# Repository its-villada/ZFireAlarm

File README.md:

# ZFireAlarm
Sistema de sensores inalámbricos a ser distribuidos sobre el edificio de la institución educativa para lograr el objetivo inicial de red inalámbrica para sirenas de incendio.

## Objetivos
- Que el alumno se familiarice con las capacidades de los equipos XBee.
- Que sea capaz de diseñar una parte de un sistema real, que luego se montará en la práctica.
- Definir un presupuesto real para implementar un sistema completo y revisar posibilidades de implementación en base a disponibilidad en el mercado.
- Adquirir nociones generales sobre el hardware y software a utilizar en aplicaciones reales, a través del desarrollo de un ejercicio práctico aplicado a sensores y actuadores remotos. 

## Software y aplicaciones
- Python: https://www.python.org/
- Python-XBee: https://pypi.python.org/pypi/XBee
- XCTU: http://www.digi.com/products/xbee-rf-solutions/xctu-software/

## Arquitectura del sistema

### Gateway
El gateway debe estar montado con un Raspberry Pi (https://www.raspberrypi.org/) incluyendo un modulo XBee. En el siguiente link pueden encontrar un ejemplo de shield para XBee en la plataforma: https://www.cooking-hacks.com/ocumentation/tutorials/xbee-arduino-raspberry-pi-tutorial/

Las características son:
- El raspberry pi a utilizar es Raspberry Pi Model B+ (B PLUS) 512MB
- Conectividad ethernet (provista a través del Raspberry pi)
- Modulo XBee pro series 2: https://cdn-shop.adafruit.com/product-files/967/p967b+datasheet.pdf
- El shield de xbee provee un conector para puerto serie (idéntico al utilizado en las placas XBoard)
- Alimentado con fuente de alimentación externa
- Led indicador de alimentación.
- Entrada para pulsador externo (activación principal de la alarma de incendio).

### Nodos

Las características de los nodos son:
- Bateria 12V 7 A/H , las mismas que se utilizan en los sistemas de alarmas hogareño.
- Led indicador estado de batería
- Conector serie (idéntico al utilizado en las placas de evaluacion XBoard)
- Salida para alimentar una sirena 12V/24V 2A.
- Conectividad wireless brindada por módulo XBee pro series 2.

## Hardware
- Sirenas incendio
- Modulos XBee pro
- Modulo Raspberri pi
- Gabinete
- Bateria 12V 7AH

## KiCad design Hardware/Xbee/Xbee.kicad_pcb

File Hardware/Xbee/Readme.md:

# Diseño en KiCad

Se utiliza una única placa con ambas funciones.
Esquemático en Xbee.pdf

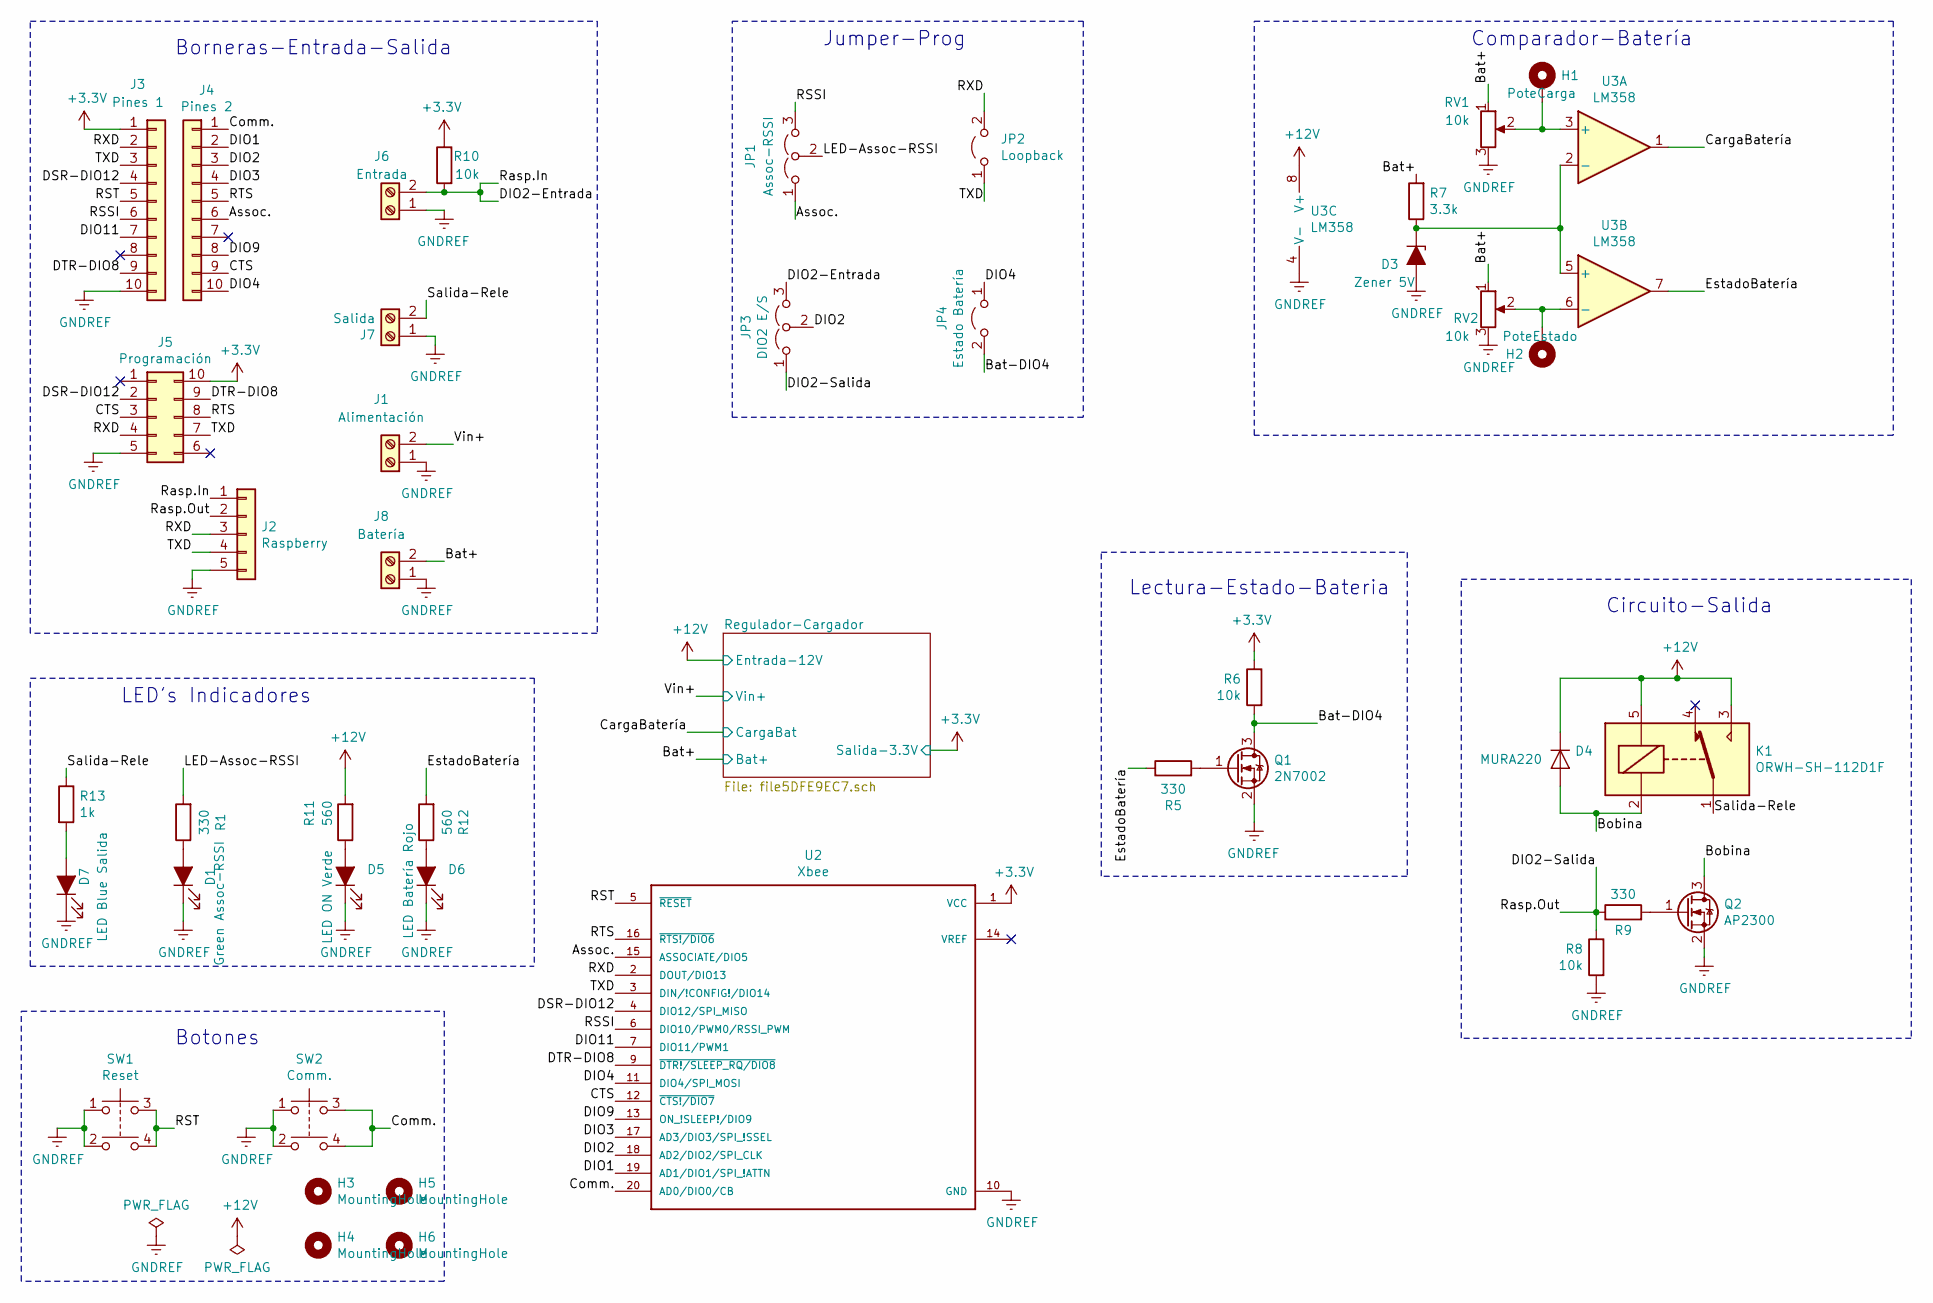
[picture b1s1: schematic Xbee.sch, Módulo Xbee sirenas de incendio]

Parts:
D1: Green Assoc-RSSI; LED_1206_3216Metric_Pad1.42x1.75mm_HandSolder
D3: Zener 5V; D_SOT-23_ANK
D4: MURA220; D_SMA_Handsoldering
D5: LED ON Verde; PinSocket_1x02_P2.54mm_Vertical
D6: LED Batería Rojo; PinSocket_1x02_P2.54mm_Vertical
D7: LED Blue Salida; LED_1206_3216Metric_Pad1.42x1.75mm_HandSolder
H1: PoteCarga; MountingHole_2.2mm_M2_DIN965_Pad
H2: PoteEstado; MountingHole_2.2mm_M2_DIN965_Pad
H3, H4, H5, H6: MountingHole; MountingHole_3.2mm_M3
J1: Alimentación; TerminalBlock_bornier-2_P5.08mm
J2: Raspberry; PinHeader_1x05_P2.54mm_Vertical
J3: Pines 1; PinSocket_1x10_P2.00mm_Vertical
J4: Pines 2; PinSocket_1x10_P2.00mm_Vertical
J5: Programación; PinSocket_2x05_P2.54mm_Horizontal
J6: Entrada; TerminalBlock_bornier-2_P5.08mm
J7: Salida; TerminalBlock_bornier-2_P5.08mm
J8: Batería; TerminalBlock_bornier-2_P5.08mm
JP1: Assoc-RSSI; PinHeader_1x03_P2.54mm_Vertical
JP2: Loopback; PinHeader_1x02_P2.54mm_Vertical
JP3: DIO2 E/S; PinHeader_1x03_P2.54mm_Vertical
JP4: Estado Batería; PinHeader_1x02_P2.54mm_Vertical
K1: ORWH-SH-112D1F; Relay_SPDT_SANYOU_SRD_Series_Form_C
Q1: 2N7002; SOT-23
Q2: AP2300; SOT-23
R1, R5, R9: 330; R_1206_3216Metric_Pad1.42x1.75mm_HandSolder
R6, R8, R10: 10k; R_1206_3216Metric_Pad1.42x1.75mm_HandSolder
R7: 3.3k; R_1206_3216Metric_Pad1.42x1.75mm_HandSolder
R11, R12: 560; R_1206_3216Metric_Pad1.42x1.75mm_HandSolder
R13: 1k; R_1206_3216Metric_Pad1.42x1.75mm_HandSolder
RV1, RV2: 10k; Potentiometer_Vishay_T73YP_Vertical
SW1: Reset; SW_TH_Tactile_Omron_B3F-10xx
SW2: Comm.; SW_TH_Tactile_Omron_B3F-10xx
U2: Xbee; DIP2200W51P200L3294H279Q20P
U3: LM358; SO-8_3.9x4.9mm_P1.27mm

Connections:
+3V3: J3.1, J5.10, R6.1, R10.1, U2.1 (VCC); also elsewhere on the board
+12V: D4.1 (K), K1.3, K1.5, R11.2, U3.8 (V+); also elsewhere on the board
/Assoc.: J4.6, JP1.1 (A), U2.15 (ASSOCIATE/DIO5)
/Bat+: J8.2, R7.2, RV1.1, RV2.1; also elsewhere on the board
/Bat-DIO4: JP4.2 (B), Q1.3 (D), R6.2
/Bobina: D4.2 (A), K1.2, Q2.3 (D)
/CTS: J4.9, J5.3, U2.12 (~CTS!/DIO7~)
/CargaBatería: U3.1; also elsewhere on the board
/Comm.: J4.1, SW2.3, SW2.4, U2.20 (AD0/DIO0/CB)
/DIO1: J4.2, U2.19 (AD1/DIO1/SPI_!ATTN)
/DIO2: J4.3, JP3.2 (C), U2.18 (AD2/DIO2/SPI_CLK)
/DIO2-Entrada: J2.1, J6.2, JP3.3 (B), R10.2
/DIO2-Salida: J2.2, JP3.1 (A), R8.1, R9.1
/DIO3: J4.4, U2.17 (AD3/DIO3/SPI_!SSEL)
/DIO4: J4.10, JP4.1 (A), U2.11 (DIO4/SPI_MOSI)
/DIO9: J4.8, U2.13 (ON_!SLEEP!/DIO9)
/DIO11: J3.7, U2.7 (DIO11/PWM1)
/DSR-DIO12: J3.4, J5.2, U2.4 (DIO12/SPI_MISO)
/DTR-DIO8: J3.9, J5.9, U2.9 (~DTR!/SLEEP_RQ/DIO8~)
/EstadoBatería: R5.1, R12.2, U3.7
/LED-Assoc-RSSI: JP1.2 (C), R1.2
/RSSI: J3.6, JP1.3 (B), U2.6 (DIO10/PWM0/RSSI_PWM)
/RST: J3.5, SW1.3, SW1.4, U2.5 (~RESET~)
/RTS: J4.5, J5.8, U2.16 (~RTS!/DIO6~)
/RXD: J2.3, J3.2, J5.4, JP2.2 (B), U2.2 (DOUT/DIO13)
/Salida-Rele: J7.2, K1.1, R13.1
/TXD: J2.4, J3.3, J5.7, JP2.1 (A), U2.3 (DIN/!CONFIG!/DIO14)
/Vin+: J1.2; also elsewhere on the board
GNDREF: D1.1 (K), D3.2 (A), D5.1 (K), D6.1 (K), D7.1 (K), J1.1, J2.5, J3.10, J5.5, J6.1, J7.1, J8.1, Q1.2 (S), Q2.2 (S), R8.2, RV1.3, RV2.3, SW1.1, SW1.2, SW2.1, SW2.2, U2.10 (GND), U3.4 (V-); also elsewhere on the board
unnamed: D1.2 (A), R1.1
unnamed: D3.1 (K), R7.1, U3.2 (-), U3.5 (+)
unnamed: D5.2 (A), R11.1
unnamed: D6.2 (A), R12.1
unnamed: D7.2 (A), R13.2
unnamed: H1.1, RV1.2, U3.3 (+)
unnamed: H2.1, RV2.2, U3.6 (-)
unnamed: Q1.1 (G), R5.2
unnamed: Q2.1 (G), R9.2

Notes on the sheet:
Borneras-Entrada-Salida
LED's Indicadores
Jumper-Prog
Circuito-Salida
Comparador-Batería
Botones
Lectura-Estado-Bateria

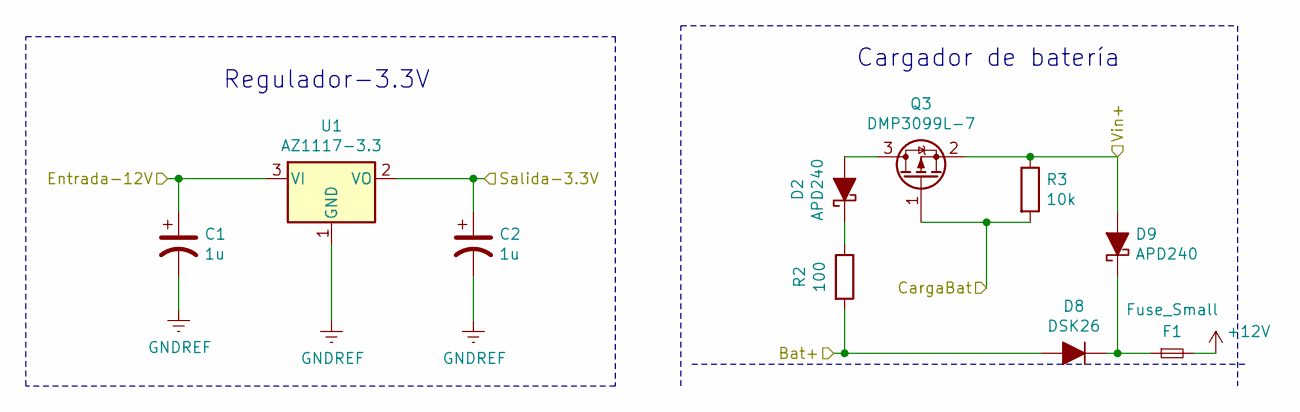
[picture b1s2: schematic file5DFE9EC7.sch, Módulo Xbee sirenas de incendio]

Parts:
C1, C2: 1u; C_0805_2012Metric_Pad1.15x1.40mm_HandSolder
D2, D9: APD240; D_SOD-123
D8: DSK26; D_SOD-123F
F1: Fuse_Small; Fuse_1206_3216Metric_Pad1.42x1.75mm_HandSolder
Q3: DMP3099L-7; SOT-23
R2: 100; R_1218_3246Metric_Pad1.22x4.75mm_HandSolder
R3: 10k; R_1206_3216Metric_Pad1.42x1.75mm_HandSolder
U1: AZ1117-3.3; SOT-223-3_TabPin2

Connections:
+3V3: C2.1, U1.2 (VO); also elsewhere on the board
+12V: C1.1, F1.2, U1.3 (VI); also elsewhere on the board
/Bat+: D8.2 (A), R2.2; also elsewhere on the board
/CargaBatería: Q3.1 (G), R3.2; also elsewhere on the board
/Vin+: D9.2 (A), Q3.2 (S), R3.1; also elsewhere on the board
GNDREF: C1.2, C2.2, U1.1 (GND); also elsewhere on the board
unnamed: D2.1 (K), R2.1
unnamed: D2.2 (A), Q3.3 (D)
unnamed: D8.1 (K), D9.1 (K), F1.1

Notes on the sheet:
Regulador-3.3V
Cargador de batería

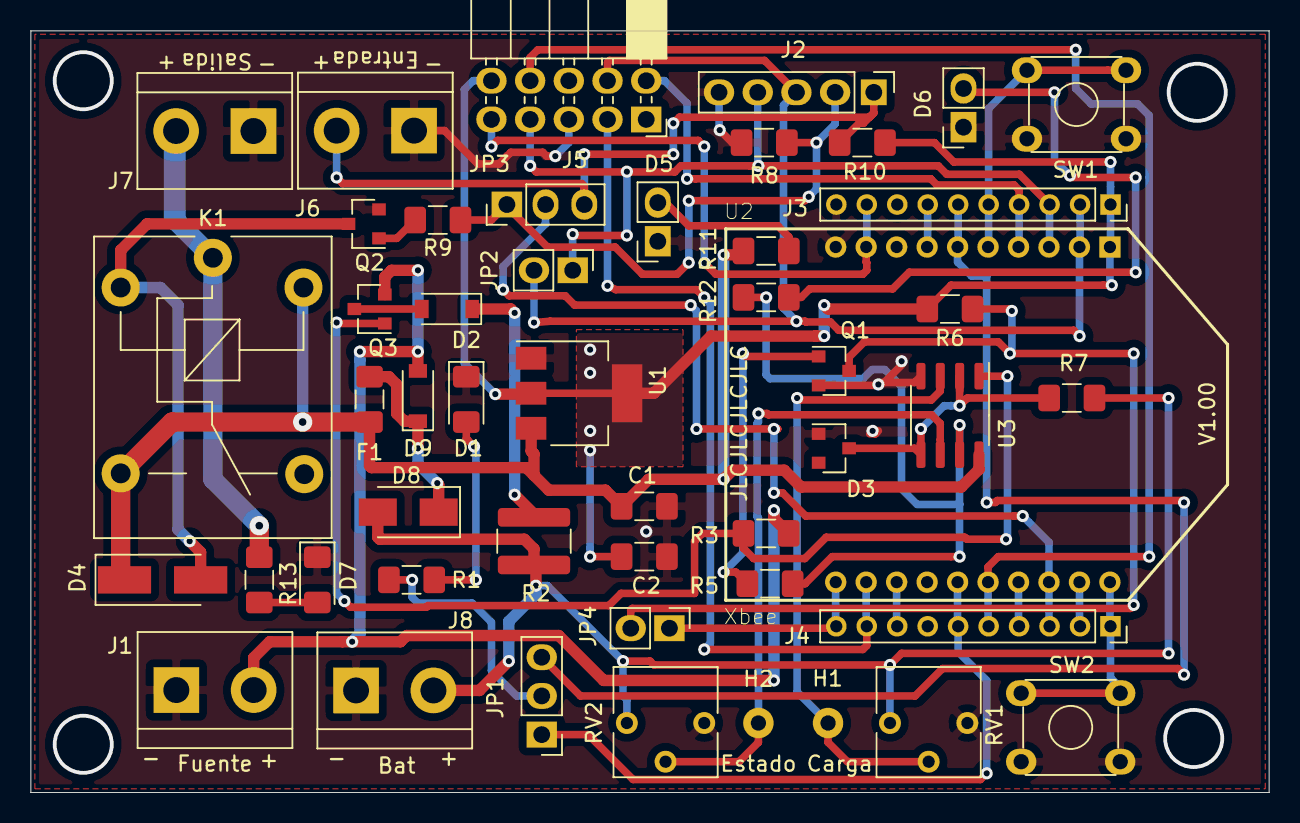
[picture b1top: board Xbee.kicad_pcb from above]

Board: 2 copper layers, 81.3 x 50.0 mm, 49 parts (0 on the bottom side), 41 nets.

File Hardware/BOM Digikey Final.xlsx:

Qty | Value | Código Proveedor 1 | Código Proveedor 2 | Package | Costo Unit. [u$] | Total [u$] | Total [$] | Dolar: | 62
2 | 1u | 399-8150-1-ND |  | 1206 | 0.19 | 0.38 | 23.56 |  |  |  | Costo Tot [u$] | 19.03
1 | Green Assoc-RSSI | 160-1169-1-ND |  | 1206 | 0.33 | 0.33 | 20.46
2 | MBR230LSTR | 1655-2311-1-ND |  | SOD-123 | 0.36 | 0.72 | 44.64 |  |  |  | Costo Tot [$] | 1179.8600000000001
1 | Zener 5V | BZX84C5V1LT3GOSCT-ND |  | SOT-23 | 0.13 | 0.13 | 8.06
1 | MURA260T3G | MURA260T3GOSCT-ND |  | SMA | 0.35 | 0.35 | 21.7 |  |  |  | Costo Tot [$] (x15) | 17697.900000000001
1 | LED ON Verde | 160-1131-ND |  | 5mm T/H | 0.27 | 0.27 | 16.740000000000002
1 | LED Rojo | 365-1189-ND |  | 5mm T/H | 0.21 | 0.21 | 13.02
1 | LED Blue Salida | 732-4989-1-ND |  | 1206 | 0.21 | 0.21 | 13.02
1 | MURA260T3G | MURA260T3GOSCT-ND |  | SMA | 0.35 | 0.35 | 21.7
1 | Fuse_Small | 507-1881-1-ND |  | 1206 | 0.28999999999999998 | 0.28999999999999998 | 17.98
1 | Alimentación | 102-6422-ND |  | 5.08mm T/H | 0.46 | 0.46 | 28.52
1 | Alimentación 2 | 102-6390-ND |  | 5.08mm T/H | 0.77 | 0.77 | 47.74
1 | Raspberry | 2057-PH1-05-UA-ND |  | 2.54mm T/H | 0.1 | 0.1 | 6.2
1 | Pines 1 | 1212-1314-ND |  | 2mm T/H | 0.91 | 0.91 | 56.42
1 | Pines 2 | 1212-1314-ND |  | 2mm T/H | 0.91 | 0.91 | 56.42
1 | Programaci√≥n | S9202-ND |  | 2.54mm T/H | 0.8 | 0.8 | 49.6
1 | Entrada | 102-6422-ND |  | 5.08mm T/H | 0.46 | 0.46 | 28.52
1 | Entrada 2 | 102-6390-ND |  | 5.08mm T/H | 0.77 | 0.77 | 47.74
1 | Salida | 102-6422-ND |  | 5.08mm T/H | 0.46 | 0.46 | 28.52
1 | Salida 2 | 102-6390-ND |  | 5.08mm T/H | 0.77 | 0.77 | 47.74
1 | Bater√≠a | 102-6422-ND |  | 5.08mm T/H | 0.46 | 0.46 | 28.52
1 | Bater√≠a 2 | 102-6390-ND |  | 5.08mm T/H | 0.77 | 0.77 | 47.74
1 | Assoc-RSSI | 1849-1003-ND |  | 2.54mm T/H | 0.1 | 0.1 | 6.2
1 | Loopback | 2057-PH1-02-UA-ND |  | 2.54mm T/H | 0.1 | 0.1 | 6.2
1 | DIO2 E/S | 1849-1003-ND |  | 2.54mm T/H | 0.1 | 0.1 | 6.2
1 | Estado Bater√≠a | 2057-PH1-02-UA-ND |  | 2.54mm T/H | 0.1 | 0.1 | 6.2
1 | ORWH-SH-112D1F | PB2029-ND |  | SPDT (1 Form C) | 1.19 | 1.19 | 73.78
1 | 2N7002NXAKR |  |  | SOT-23 |  | 0 | 0 | Revisar
1 | AP2300 | 1727-8643-1-ND |  | SOT-23 | 0.1 | 0.1 | 6.2 | Revisar
1 | DMP3099L-7 | DMP3099L-7DICT-ND |  | SOT-23 | 0.34 | 0.34 | 21.080000000000002 | Revisar
3 | 330 | RMCF1206JT330RCT-ND |  | 1206 | 0.1 | 0.30000000000000004 | 18.600000000000001
1 | 100 | 311-100FRCT-ND |  | 1206 | 0.1 | 0.1 | 6.2
4 | 10k | 311-10KERCT-ND |  | 1206 | 0.1 | 0.4 | 24.8
1 | 3.3k | RMCF1206JT3K30CT-ND |  | 1206 | 0.1 | 0.1 | 6.2
2 | 560 | RMCF1206JT560RCT-ND |  | 1206 | 0.1 | 0.2 | 12.4
1 | 1k | 311-1.0KERCT-ND |  | 1206 | 0.1 | 0.1 | 6.2
2 | 10k | CT6EP103-ND |  | CT-6 | 0.81 | 1.62 | 100.44000000000001 | Preset
2 | Switch SPST NO | SW401-ND |  | SPST-NO | 0.3 | 0.6 | 37.199999999999996
1 | AZ1117-3.3 | AZ1117EH-3.3TRG1DICT-ND |  | SOT-223 | 0.42 | 0.42 | 26.04
2 | Pines Xbee | 1212-1314-ND |  | 2mm T/H | 0.91 | 1.82 | 112.84
1 | LM358 | 497-1591-1-ND |  | SO-8 | 0.46 | 0.46 | 28.52

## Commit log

2019-02-28 Initial
2019-04-10 renombrado: Hardware (deprecated)/Readme.md -> Hardware_(deprecated)/Readme.md
2019-04-10 Hardware deprecated
2019-04-10 Upload files to deprecated
2019-04-10 Capturas
2019-04-10 Hardware en KiCad
2019-04-10 Se agrega esquemático en PDF
2019-07-31 Testing sync
2019-07-31 Footprint
2019-07-31 PCB design
2019-08-02 WinPC
2019-08-02 PCB footprint placement
2019-08-05 Add config image
2019-08-07 Started routing
2019-08-07 Routing
2019-08-07 Routing2
2019-08-07 SMD footprint
2019-08-07 SMD components
2019-08-09 Change names
2019-08-14 SMD footprints, change LED's
2019-08-28 MOSFET, R SMD
2019-09-06 Sheets-Text
2019-09-25 Battery Charger
2019-10-02 Added Diodes Footprints
2019-10-02 PCB Component Placement
2019-10-07 Add Mejoras
2019-10-09 Add Fuse
2019-10-11 Localización de componentes
2019-10-11 Localización 2
2019-10-18 Comienzo de ruteo
2019-10-18 Ruteo, agregado de plano masa
2019-10-21 Serigrafía, pistas, Gerber
2019-10-21 Gerber2
2019-10-23 Change footprints
2019-10-25 Change footprints 2
2019-10-28 Footprints 3
2019-10-30 SMD Routing
2019-10-30 SMD2 Serigrafia
2019-11-01 Final V1.0
2019-11-01 Final V1.0 Gerber and BOM Digikey
2019-11-04 Final V1.0 Serigrafía
2019-11-15 BOM actualizada
2019-11-15 Actualización BOM + Final Gerber
2019-11-15 BOM Final + Gerbers finales
